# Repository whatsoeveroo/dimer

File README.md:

# Dimer

A tabletop pet robot, under 20 cm: two tracks, a head that turns to look around, table-edge sensing,
a front shovel, a face display, and voice through the OpenAI API.

| Folder | What is in it |
|---|---|
| `docs/` | `BOM.md` buying list with one product link per part. `ASSEMBLY.md` step-by-step assembly guideline. `JLCPCB.md` how to order the built board. |
| `cad/` | `dimer_frame.py` generates the frame guideline and places every part. `dimer_components.py` holds the models of the bought parts. `cad/step/` has one STEP per printed part, `dimer_guideline_assembly.step` with everything in place, and `components/` with one STEP per bought part. |
| `pcb/` | `make_board.py` generates the v0.2 board (all chips and connectors fitted by JLCPCB). Upload `dimer_main_gerbers_JLCPCB.zip`, `dimer_main_BOM_JLCPCB.csv` and `dimer_main_CPL_JLCPCB.csv`. `dimer_main.kicad_pcb` opens in KiCad, `dimer_main_3d.step` is the board in 3D, `drc_report.txt` is the rule check. |
| `web/` | `build_page.py` and `template.html` build the web page (`dimer_build_plan.html`) and `docs/ASSEMBLY.md` from one list of steps. |
| `firmware/` | `dimer_pins.h` pin map for the ESP32-S3. |

## Status (v0.2, no soldering)

- Buying list: every part arrives with pins or wires attached. Links checked on AliExpress on 2026-11-16. Track set not chosen yet.
- Assembly guide: written for the v0.2 board and frame.
- Frame: rough guideline only. Holes for the round switch, charging socket and distance sensor use typical sizes. Some parts have no fixing designed yet.
- PCB v0.2: routed with freerouting, KiCad rule check shows 0 clearance errors and 0 unconnected pads. Not yet built or powered. Order it assembled, see `docs/JLCPCB.md`.
- Firmware: pin map only.

## Regenerating

```
pip install cadquery shapely numpy
python cad/dimer_frame.py        # frame STEP files
python pcb/make_board.py         # board, rule check, Gerbers (needs KiCad 7 or newer and freerouting)
python cad/dimer_frame.py web/mesh.json && python web/build_page.py   # web page and docs/ASSEMBLY.md
```

Axes in the CAD: X forward, Y left, Z up, table at Z = 0, units mm.

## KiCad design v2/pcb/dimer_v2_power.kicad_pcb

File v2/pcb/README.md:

# Dimer V2 power board (r1)

One small board, made and fully soldered by JLCPCB, that replaces the charger module,
the slide switch, the DRV8833 module and the PCF8574 module of the first V2 list.
r1 includes the fixes from an outside design review (see the end of this page).
No power wiring to solder: the battery plugs in, USB-C and the switch are on the board.

| | |
|---|---|
| Size | 39.5 x 33 mm, 2 layers, 1.6 mm, one M2 screw hole |
| Where | Flat in the electronics bay at z = 20.2 mm, on two ledges of the side walls, above the battery and the left motor. One M2 x 6 self-tapping screw into the pillar at the rear right; two lips under the lid hold the front edge. |
| Battery | 1S LiPo with protection board and a JST PH 2.0 plug (`+` is marked) |
| Charging | USB-C on the rear wall, TP4056, about 0.4 A (2.5 h for 1000 mAh). Charge with the switch off: with the robot running the charger may not stop on its own. Red light = charging, green = full. You see them through two holes in the lid. |
| Switch | Slide switch in the rear wall slot (use a fingernail or a toothpick). It only drives a P-MOSFET (AO3401A), so it never carries motor current. |
| 5 V | MT3608 boost, about 1 A steady, with 66 uF of output capacitors for servo and Wi-Fi bursts: servo, XIAO brain, amplifier. The head gets it through a diode, so plugging USB into the XIAO cannot back-feed the board. |
| 3.3 V | AP2112K-3.3 from the 5 V: expander, edge sensors, I2C pull-ups |
| Motors | DRV8833 on the switched battery. It sleeps until the firmware wakes it, so the tracks cannot move at power-up. |
| Expander | PCA9534 at I2C address 0x20 (same pins as PCF8574T, but starts with every pin as an input): P0/P1 motor directions, P2/P3 edge sensors, P4 motor sleep, P5-P7 unused |

## Plugs (2.54 mm pins for jumper wires)

| Label | Pins | Goes to |
|---|---|---|
| HEAD (J8) | 5V, G, DA, CL | XIAO 5V (and the amplifier, with a splitter), GND, D4 (SDA), D5 (SCL) |
| SV G 3V G (J9) | SV, G, 3V, G | XIAO D2 (servo signal), GND for the head (screen and amplifier, with a splitter); 3V and G spare |
| PL PR (J11) | 2 pins | XIAO D0 (PWM left), D1 (PWM right) |
| TILT | G, 5V, S | SG90 servo plug (brown wire on G) |
| EDGE L / EDGE R | V, G, S | TCRT5000 VCC, GND, DO |
| MOT L / MOT R | 2 pins | N20 motor tabs (swap the two wires if a track runs backwards) |
| BAT | +, - | battery |

The firmware pin map is in `v2/firmware/dimer_v2_pins.h`.

## Files

| File | What it is |
|---|---|
| `dimer_v2_power_gerbers_JLCPCB.zip` | Upload this as the PCB |
| `dimer_v2_power_BOM_JLCPCB.csv` | Parts list for assembly |
| `dimer_v2_power_CPL_JLCPCB.csv` | Part positions for assembly |
| `dimer_v2_power.kicad_pcb` | The board, opens in KiCad 7 or newer |
| `drc_report.txt` | KiCad design-rule check of the routed board |
| `make_board_v2.py` | Builds all of the above (KiCad 7 + freerouting) |
| `board_parts_json.py` | Writes `dimer_v2_power_parts.json`, from which the frame script draws the board in the 3D model |

## Ordering at JLCPCB

1. Go to jlcpcb.com, **Order now**, and upload `dimer_v2_power_gerbers_JLCPCB.zip`. It reads 39.5 x 33 mm, 2 layers.
2. Keep the defaults: FR-4, 1.6 mm, HASL (lead free if you like), any colour. Quantity 5 or 10.
3. Turn on **PCB Assembly**. Choose **Standard** (the pin headers and the battery plug are through-hole, Economic does not do those), **Top side**, tooling holes **Added by JLCPCB**, and the same quantity.
4. Upload `dimer_v2_power_BOM_JLCPCB.csv` and `dimer_v2_power_CPL_JLCPCB.csv`.
5. On the parts page, pick a part for each row that has no match (see the list below). Search the text in the row's comment.
6. On the placement page, look at every chip and the two LEDs. The dot (pin 1) must sit on the marked corner. If one is turned the wrong way, rotate it there; JLCPCB fixes it before building.
7. Order. JLCPCB checks the files again and emails if anything is unclear.

### Parts to check on the parts page

Every LCSC number in the BOM was checked on jlcpcb.com on 17 Nov 2026 and was in stock. The step-by-step order sheet, with the parts table and the placement checks, is in [ORDER_AT_JLCPCB.md](ORDER_AT_JLCPCB.md). Two swaps since the review: U5 is TI's TCA9534DWR (C2870609), the twin of the PCA9534 with the same pins, address and registers, because only one PCA9534 in the wide package was in stock; D2 is KT-0603G (C12624).

### Rough cost (USD, not a live quote)

| | 5 boards | 10 boards |
|---|---|---|
| Bare boards | 2 | 5 |
| Assembly setup + stencil (Standard) | 33 | 33 |
| Extended-part fees, about 10 parts at $3 | 30 | 30 |
| Parts, about $3 a board | 15 | 30 |
| Through-hole soldering, about 33 joints a board | 3 | 6 |
| Shipping (cheapest) | 10 to 20 | 10 to 20 |
| **Total** | **about $95 to $105, so $20 a board** | **about $115 to $125, so $12 a board** |

The fixed fees are most of the price, so more boards in one order are much cheaper each.

## Before the first power-up

1. Check the battery plug: red wire on `+`.
2. Plug in USB-C with no battery: nothing should get warm. With the battery: the red light comes on.
3. Switch on with nothing else plugged in and measure: 5V pin about 5.1 V, I2C 3V pin 3.3 V.
4. Then plug in the servo, the sensors, the motors and the head.

## Outside review (GPT-6 Astra, 17 Nov 2026) and what changed

| Finding | What r1 does |
|---|---|
| The PCF8574 starts with its pins high, so the motors could run backwards at power-up | Swapped to the PCA9534 family, built as TI's TCA9534 (same pins and address, starts as inputs). Pull-downs on both direction lines, and the motor driver's sleep pin is on expander P4 with a pull-down: the tracks stay still until the firmware wakes them. |
| The XIAO's 5V pin is its USB power, so USB programming would back-feed the board | The head's 5 V goes through a B5819W diode. |
| 5 V bursts (servo, camera, Wi-Fi, speaker) | Output capacitors 3 x 22 uF instead of 3 x 10 uF, inductor rated 3 A or more. Measure the 5 V while the servo moves and the speaker plays before trusting it. |
| AMS1117 needs a big output capacitor to be stable | Swapped to AP2112K-3.3. |
| TP4056 runs hot at 0.6 A | Charge current 0.4 A. Charge with the switch off. |
| DRV8833 VINT capacitor should be 2.2 uF | Done. (Its fault line stays unconnected: there was no room to route it.) |
| Head power and ground need splitting | Three 1-to-3 dupont splitters in the buying list. |
| ST7735 reset pin is not driven | Firmware sends the software reset at start-up (noted in the pin map). |
| Not changed: a bigger boost chip (TPS61088), load sharing for the charger, rear edge sensors | Kept the board simple and cheap for the first build; revisit if the 5 V measurement shows dips. |

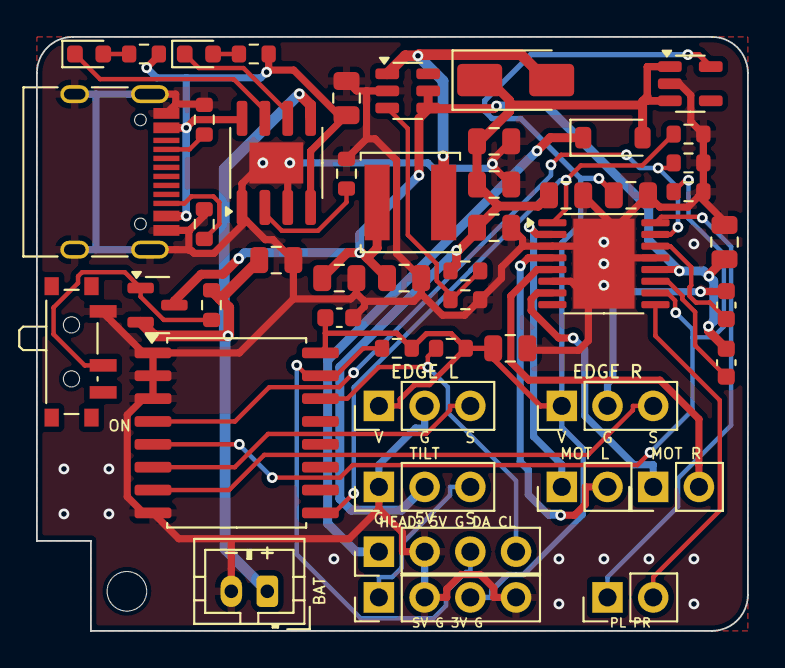
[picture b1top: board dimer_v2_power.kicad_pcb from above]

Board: 2 copper layers, 39.5 x 33.0 mm, 50 parts (0 on the bottom side), 33 nets.

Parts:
C1, C2, C3, C4, C8, C9, C10, C11: 10uF 25V; C_0805_2012Metric
C5, C6, C7: 22uF 10V; C_0805_2012Metric
C12: 10nF; C_0603_1608Metric
C13: 2.2uF 10V; C_0603_1608Metric
C14: 100nF; C_0603_1608Metric
D1: LED red 0603; LED_0603_1608Metric
D2: LED green 0603; LED_0603_1608Metric
D3: SS34; D_SMA
D4: B5819W; D_SOD-123
H1: M2; MountingHole_2.2mm_M2
J1: USB-C 16P TYPE-C-31-M-12; USB_C_Receptacle_HRO_TYPE-C-31-M-12
J2: JST PH 2P vertical B2B-PH-K-S; JST_PH_B2B-PH-K_1x02_P2.00mm_Vertical
J3, J4, J5: Pin header 1x3 2.54mm; PinHeader_1x03_P2.54mm_Vertical
J6, J7, J11: Pin header 1x2 2.54mm; PinHeader_1x02_P2.54mm_Vertical
J8, J9: Pin header 1x4 2.54mm; PinHeader_1x04_P2.54mm_Vertical
L1: 4.7uH 5040 Isat 3.8A (FNR5040S4R7MT); L_Changjiang_FNR5040S
Q1: AO3401A P-MOSFET; SOT-23
R1, R2: 5.1k; R_0603_1608Metric
R3: 3k; R_0603_1608Metric
R4, R5: 1k; R_0603_1608Metric
R6: 100k; R_0603_1608Metric
R7: 75k; R_0603_1608Metric
R8, R11, R12, R13: 10k; R_0603_1608Metric
R9, R10: 4.7k; R_0603_1608Metric
SW1: Slide switch SPDT PCM12SMTR; SW_SPDT_PCM12
U1: TP4056 ESOP-8; SOIC-8-1EP_3.9x4.9mm_P1.27mm_EP2.29x3mm
U2: MT3608; SOT-23-6
U3: AP2112K-3.3; SOT-23-5
U4: DRV8833PWP; HTSSOP-16-1EP_4.4x5mm_P0.65mm_EP3.4x5mm_Mask2.46x2.31mm
U5: TCA9534DWR SO-16 wide (PCA9534 twin); SOIC-16W_7.5x10.3mm_P1.27mm

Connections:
3V3: C9.1, C10.1, C14.1, J3.1, J4.1, J9.3, R9.2, R10.2, U3.5, U5.16
5V: C5.1, C6.1, C7.1, C8.1, D3.1, D4.2, J5.2, R7.1, U3.1, U3.3
BST_FB: R7.2, R8.1, U2.3
BST_SW: D3.2, L1.2, U2.1
CC1: J1.A5, R1.1
CC2: J1.B5, R2.1
CHRG: D1.1, U1.7
DIR_L: R12.1, U4.15, U5.4
DIR_R: R13.1, U4.10, U5.5
DRV_SLEEP: R11.1, U4.1, U5.9
DRV_VCP: C12.1, U4.11
DRV_VINT: C13.1, U4.14
EDGE_L: J3.3, U5.6
EDGE_R: J4.3, U5.7
GATE: Q1.1, R6.1, SW1.2
GND: C1.2, C2.2, C3.2, C4.2, C5.2, C6.2, C7.2, C8.2, C9.2, C10.2, C11.2, C13.2, C14.2, J1.A1, J1.A12, J1.B1, J1.B12, J1.S1, J2.2, J3.2, J4.2, J5.1, J8.2, J9.2, J9.4, R1.2, R2.2, R3.2, R8.2, R11.2, R12.2, R13.2, SW1.1, U1.1, U1.3, U1.9, U2.2, U3.2, U4.3, U4.6, U4.13, U4.17, U5.1, U5.2, U5.3, U5.8
HEAD_5V: D4.1, J8.1
LED_G: D2.2, R5.1
LED_R: D1.2, R4.1
MOTL_A: J6.1, U4.2
MOTL_B: J6.2, U4.4
MOTR_A: J7.1, U4.7
MOTR_B: J7.2, U4.5
PROG: R3.1, U1.2
PWM_L: J11.1, U4.16
PWM_R: J11.2, U4.9
SCL: J8.4, R10.1, U5.14
SDA: J8.3, R9.1, U5.15
SERVO: J5.3, J9.1
STDBY: D2.1, U1.6
VBAT: C2.1, J2.1, Q1.2, R6.2, U1.5
VBUS: C1.1, J1.A4, J1.A9, J1.B4, J1.B9, R4.2, R5.2, U1.4, U1.8
VSYS: C3.1, C4.1, C11.1, C12.2, L1.1, Q1.3, U2.4, U2.5, U4.12

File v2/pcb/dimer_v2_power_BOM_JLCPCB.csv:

Comment,Designator,Footprint,LCSC Part #
10uF 25V,"C1,C2,C3,C4,C8,C9,C10,C11",C_0805_2012Metric,C15850
22uF 10V,"C5,C6,C7",C_0805_2012Metric,C45783
10nF,C12,C_0603_1608Metric,C57112
2.2uF 10V,C13,C_0603_1608Metric,C23630
100nF,C14,C_0603_1608Metric,C14663
LED red 0603,D1,LED_0603_1608Metric,C2286
LED green 0603,D2,LED_0603_1608Metric,C12624
SS34,D3,D_SMA,C8678
B5819W,D4,D_SOD-123,C8598
USB-C 16P TYPE-C-31-M-12,J1,USB_C_Receptacle_HRO_TYPE-C-31-M-12,C165948
JST PH 2P vertical B2B-PH-K-S,J2,JST_PH_B2B-PH-K_1x02_P2.00mm_Vertical,C131337
Pin header 1x3 2.54mm,"J3,J4,J5",PinHeader_1x03_P2.54mm_Vertical,C49257
Pin header 1x2 2.54mm,"J6,J7,J11",PinHeader_1x02_P2.54mm_Vertical,C124375
Pin header 1x4 2.54mm,"J8,J9",PinHeader_1x04_P2.54mm_Vertical,C124378
4.7uH 5040 Isat 3.8A (FNR5040S4R7MT),L1,L_Changjiang_FNR5040S,C167963
AO3401A P-MOSFET,Q1,SOT-23,C15127
5.1k,"R1,R2",R_0603_1608Metric,C23186
3k,R3,R_0603_1608Metric,C4211
1k,"R4,R5",R_0603_1608Metric,C21190
100k,R6,R_0603_1608Metric,C25803
75k,R7,R_0603_1608Metric,C23242
10k,"R8,R11,R12,R13",R_0603_1608Metric,C25804
4.7k,"R9,R10",R_0603_1608Metric,C23162
Slide switch SPDT PCM12SMTR,SW1,SW_SPDT_PCM12,C221841
TP4056 ESOP-8,U1,SOIC-8-1EP_3.9x4.9mm_P1.27mm_EP2.29x3mm,C16581
MT3608,U2,SOT-23-6,C84817
AP2112K-3.3,U3,SOT-23-5,C51118
DRV8833PWP,U4,HTSSOP-16-1EP_4.4x5mm_P0.65mm_EP3.4x5mm_Mask2.46x2.31mm,C50506
TCA9534DWR SO-16 wide (PCA9534 twin),U5,SOIC-16W_7.5x10.3mm_P1.27mm,C2870609

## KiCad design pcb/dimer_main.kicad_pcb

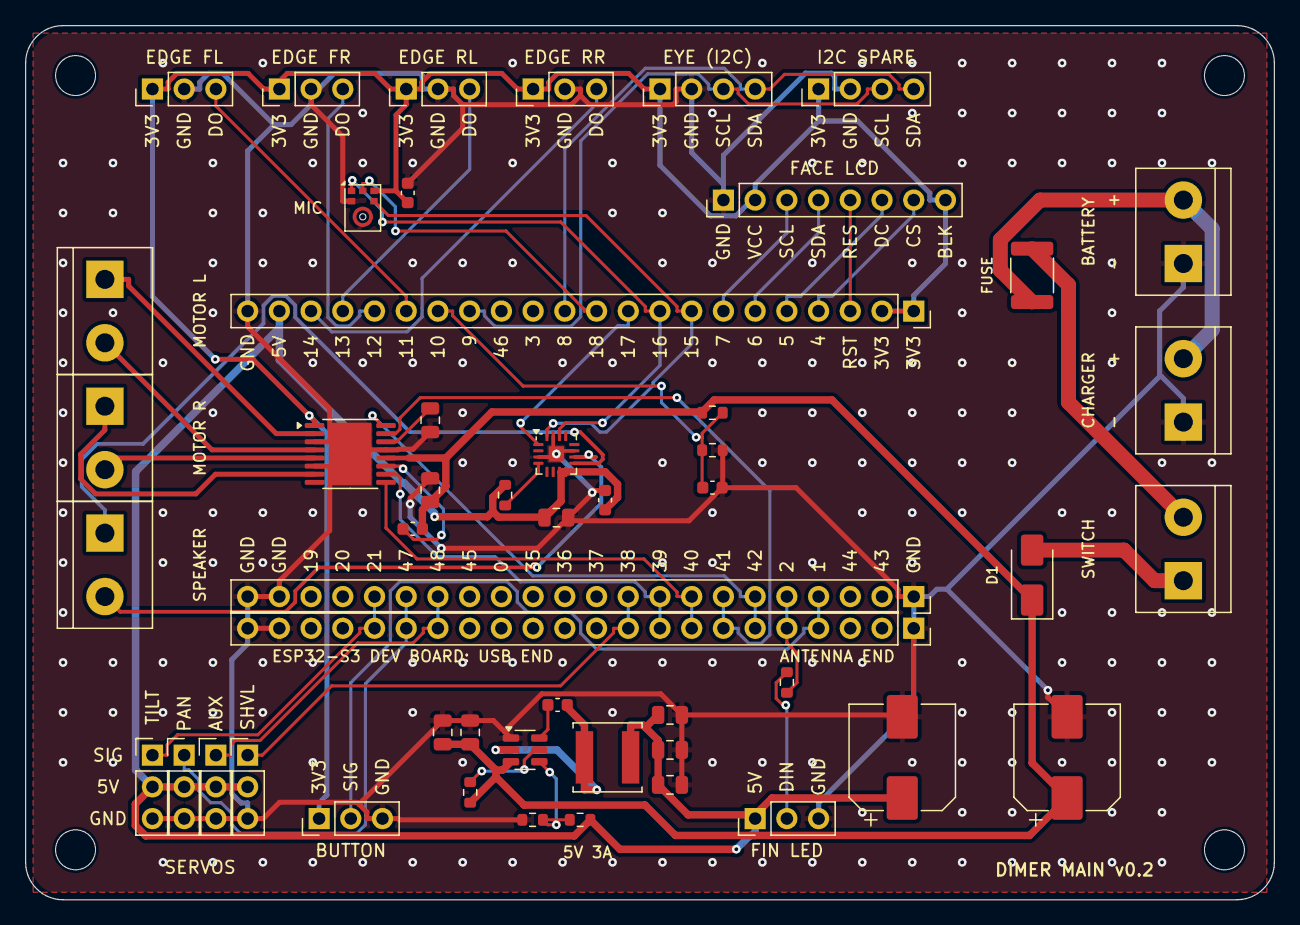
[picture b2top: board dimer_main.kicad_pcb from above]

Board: 2 copper layers, 100.0 x 70.0 mm, 55 parts (0 on the bottom side), 47 nets.

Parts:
C1, C2: 470uF 16V; CP_Elec_8x10
C3, C8, C9, C15: 100nF; C_0603_1608Metric
C4, C6, C7, C10, C11, C12, C13, C14: 10uF 25V; C_0805_2012Metric
C5: 10nF; C_0603_1608Metric
D1: SS34; D_SMA
F1: PTC 3A 16V; Fuse_1812_4532Metric
H1, H2, H3, H4: M3; MountingHole_3.2mm_M3
J1, J2, J3, J4, J5, J6: Screw terminal 2P 5.08mm; TerminalBlock_bornier-2_P5.08mm
J10, J11, J12, J13, J20, J21, J22, J23, J24, J26: Pin header 1x3 2.54mm; PinHeader_1x03_P2.54mm_Vertical
J14, J15: Pin header 1x4 2.54mm; PinHeader_1x04_P2.54mm_Vertical
J18: Pin header 1x8 2.54mm; PinHeader_1x08_P2.54mm_Vertical
L1: 3.3uH FNR5040S3R3NT; L_Changjiang_FNR5040S
R1, R4, R7: 100k; R_0603_1608Metric
R2: 47k; R_0603_1608Metric
R3: 330R; R_0603_1608Metric
R5: 56k; R_0603_1608Metric
R6: 10k; R_0603_1608Metric
U1A, U1B, U1C: Socket 1x22 2.54mm; PinSocket_1x22_P2.54mm_Vertical
U2: DRV8833PWP; HTSSOP-16-1EP_4.4x5mm_P0.65mm_EP3.4x5mm_Mask2.46x2.31mm
U3: MAX98357AETE+T; TQFN-16-1EP_3x3mm_P0.5mm_EP1.23x1.23mm
U4: TPS563201DDCR; SOT-23-6
U5: ICS-43434; InvenSense_ICS-43434-6_3.5x2.65mm

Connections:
3V3: C9.1, J10.1, J11.1, J12.1, J13.1, J14.1, J15.1, J18.2, J18.8, J24.1, U1A.1, U1A.2, U2.1, U5.5
5V: C1.1, C7.1, C8.1, C12.1, C13.1, C14.1, J20.2, J21.2, J22.2, J23.2, J26.1, L1.2, R4.2, R5.1, U1A.21, U3.7, U3.8
AMP_SD: R4.1, U3.4
BAT+: F1.1, J1.2, J2.2
BTN: J24.2, U1B.4, U1C.4
BUCK_BST: C15.1, U4.6
BUCK_EN: R7.2, U4.5
BUCK_FB: R5.2, R6.1, U4.4
BUCK_SW: C15.2, L1.1, U4.2
DRV_VCP: C5.1, U2.11
DRV_VINT: C6.2, U2.14
EDGE_FL: J10.3, U1A.17
EDGE_FR: J11.3, U1A.18
EDGE_RL: J12.3, U1A.19
EDGE_RR: J13.3, U1A.20
FUSED: F1.2, J3.2
GND: C1.2, C2.2, C3.2, C4.2, C6.1, C7.2, C8.2, C9.2, C10.2, C11.2, C12.2, C13.2, C14.2, J1.1, J2.1, J10.2, J11.2, J12.2, J13.2, J14.2, J15.2, J18.1, J20.3, J21.3, J22.3, J23.3, J24.3, J26.3, R2.2, R6.2, U1A.22, U1B.1, U1B.21, U1B.22, U1C.1, U1C.21, U1C.22, U2.3, U2.6, U2.13, U2.17, U3.3, U3.11, U3.15, U3.17, U4.1, U5.2, U5.3
I2C_SCL: J14.3, J15.3, U1A.15
I2C_SDA: J14.4, J15.4, U1A.12
I2S_BCLK: U1A.8, U3.16, U5.4
I2S_DIN: U1A.11, U5.6
I2S_DOUT: U1A.10, U3.1
I2S_WS: U1A.9, U3.14, U5.1
LCD_CS: J18.7, U1A.4
LCD_DC: J18.6, U1A.5
LCD_MOSI: J18.4, U1A.6
LCD_SCK: J18.3, U1A.7
LED_DATA: R3.1, U1B.5, U1C.5
LED_DIN: J26.2, R3.2
MOTL_A: J4.1, U2.2
MOTL_B: J4.2, U2.4
MOTR_A: J5.1, U2.7
MOTR_B: J5.2, U2.5
MOT_AIN1: U1B.6, U1C.6, U2.16
MOT_AIN2: U1B.7, U1C.7, U2.15
MOT_BIN1: U1B.8, U1C.8, U2.9
MOT_BIN2: U1B.9, U1C.9, U2.10
RST: J18.5, U1A.3
SERVO_AUX: J22.1, U1B.16, U1C.16
SERVO_PAN: J21.1, U1B.17, U1C.17
SERVO_SHOVEL: J23.1, U1B.10, U1C.10
SERVO_TILT: J20.1, U1B.18, U1C.18
SPK+: J6.1, U3.9
SPK-: J6.2, U3.10
SW_B: D1.2, J3.1
VBAT_SENSE: C3.1, R1.2, R2.1, U1A.16
VSW: C2.1, C4.1, C5.2, C10.1, C11.1, D1.1, R1.1, R7.1, U2.12, U4.3

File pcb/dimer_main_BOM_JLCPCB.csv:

Comment,Designator,Footprint,LCSC Part #
470uF 16V,"C1,C2",CP_Elec_8x10,C82006
100nF,"C3,C8,C9,C15",C_0603_1608Metric,C14663
10uF 25V,"C4,C6,C7,C10,C11,C12,C13,C14",C_0805_2012Metric,C15850
10nF,C5,C_0603_1608Metric,C57112
SS34,D1,D_SMA,C8678
PTC 3A 16V,F1,Fuse_1812_4532Metric,C702820
Screw terminal 2P 5.08mm,"J1,J2,J3,J4,J5,J6",TerminalBlock_bornier-2_P5.08mm,C474881
Pin header 1x3 2.54mm,"J10,J11,J12,J13,J20,J21,J22,J23,J24,J26",PinHeader_1x03_P2.54mm_Vertical,C49257
Pin header 1x4 2.54mm,"J14,J15",PinHeader_1x04_P2.54mm_Vertical,C124378
Pin header 1x8 2.54mm,J18,PinHeader_1x08_P2.54mm_Vertical,C124381
3.3uH FNR5040S3R3NT,L1,L_Changjiang_FNR5040S,C167960
100k,"R1,R4,R7",R_0603_1608Metric,C25803
47k,R2,R_0603_1608Metric,C25819
330R,R3,R_0603_1608Metric,C23138
56k,R5,R_0603_1608Metric,C23206
10k,R6,R_0603_1608Metric,C25804
Socket 1x22 2.54mm,"U1A,U1B,U1C",PinSocket_1x22_P2.54mm_Vertical,C2886702
DRV8833PWP,U2,HTSSOP-16-1EP_4.4x5mm_P0.65mm_EP3.4x5mm_Mask2.46x2.31mm,C50506
MAX98357AETE+T,U3,TQFN-16-1EP_3x3mm_P0.5mm_EP1.23x1.23mm,C910544
TPS563201DDCR,U4,SOT-23-6,C116592
ICS-43434,U5,InvenSense_ICS-43434-6_3.5x2.65mm,C5656610

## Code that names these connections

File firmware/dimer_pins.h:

// Dimer main board v0.2 - pin map for ESP32-S3-DevKitC-1 (N16R8)
// Matches pcb/make_board.py. GPIO numbers, not header positions.
#pragma once

// Tracks (DRV8833 motor driver: two inputs per motor, PWM one, hold the other low)
#define PIN_MOT_AIN1 42   // left track
#define PIN_MOT_AIN2 41
#define PIN_MOT_BIN1 40   // right track
#define PIN_MOT_BIN2 39

// Servos (5 V power from the buck converter, 3.3 V signal is fine)
#define PIN_SERVO_PAN    47   // head left/right
#define PIN_SERVO_TILT   21   // head up/down (optional)
#define PIN_SERVO_SHOVEL 38   // may also blink the on-board RGB LED on some dev boards
#define PIN_SERVO_AUX    48   // spare; on-board RGB LED on most clones

// Table-edge sensors (TCRT5000 module, DO pin). HIGH = no table under the sensor.
#define PIN_EDGE_FL 11
#define PIN_EDGE_FR 12
#define PIN_EDGE_RL 13
#define PIN_EDGE_RR 14

// Face display (ST7789 SPI). RES is wired to the board reset, BLK to 3V3.
#define PIN_LCD_CS   4
#define PIN_LCD_DC   5
#define PIN_LCD_MOSI 6
#define PIN_LCD_SCK  7

// Audio (I2S). Microphone and amplifier share the two clock lines.
#define PIN_I2S_BCLK 15
#define PIN_I2S_WS   16
#define PIN_I2S_DOUT 17   // to the on-board MAX98357A (speaker)
#define PIN_I2S_DIN  18   // from the on-board ICS-43434 microphone

// EYE plug: TOF200F distance sensor (I2C, or UART on the same two pins), optional MPU6050 on the spare plug
#define PIN_I2C_SDA 8
#define PIN_I2C_SCL 9

// Misc
#define PIN_VBAT_SENSE 10  // battery / 3.13 (100k : 47k divider), ADC1
#define PIN_BUTTON     1   // to GND, use INPUT_PULLUP
#define PIN_LED_DATA   2   // fin LED strip (WS2812) through 330R
#define PIN_UART_TX    43
#define PIN_UART_RX    44

#define VBAT_DIVIDER   3.128f   // (100k + 47k) / 47k
#define VBAT_LOW_VOLTS 6.4f     // stop driving below this (2S Li-ion)

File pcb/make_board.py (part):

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for j, nm in enumerate(["SIG", "5V", "GND"]):
    text(nm, 6.6, y0 - 5.08 + 2.54 * j)
text("SERVOS", 13.97, 67.4)
header("J24", "BUTTON", 23.5, y0, ["3V3", "SIG", "GND"], ["3V3", "BTN", "GND"], label_side=-1, title="BUTTON")
header("J26", "LED_STRIP", 58.42, y0, ["5V", "DIN", "GND"], ["5V", "LED_DIN", "GND"], label_side=-1, title="FIN LED")
res("R3", "330R", 60.96, 52.6, 90, "LED_DATA", "LED_DIN", "C23138")

# ---------------- motor driver (under the dev board) ----------------
smd("Package_SO.pretty", "HTSSOP-16-1EP_4.4x5mm_P0.65mm_EP3.4x5mm_Mask2.46x2.31mm", "U2", "DRV8833PWP", 26.0, 34.3, 0,
    {"1": "3V3", "2": "MOTL_A", "3": "GND", "4": "MOTL_B", "5": "MOTR_B", "6": "GND", "7": "MOTR_A", "9": "MOT_BIN1", "10": "MOT_BIN2",
     "11": "DRV_VCP", "12": "VSW", "13": "GND", "14": "DRV_VINT", "15": "MOT_AIN2", "16": "MOT_AIN1", "17": "GND"}, "C50506")
pd = [p for p in board.FindFootprintByReference("U2").Pads() if p.GetNumber() == "12"][0].GetPosition()   # thin escape from the motor-supply pin; the wide VSW track joins its end
t = pcbnew.PCB_TRACK(board); t.SetStart(pd); t.SetEnd(P(30.7, ToMM(pd.y))); t.SetWidth(FromMM(0.35)); t.SetLayer(pcbnew.F_Cu); t.SetNet(net("VSW")); board.Add(t)
cap("C4", "10uF 25V", 32.4, 37.2, 90, "VSW", "GND", **C10U)
cap("C5", "10nF", 31.0, 40.3, 0, "DRV_VCP", "VSW", lcsc="C57112")
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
